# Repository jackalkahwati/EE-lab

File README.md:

# EE-lab

FirstLight: a prompt-to-hardware pipeline (routed, DRC-gated PCBAs plus CAD enclosures, simulation, firmware, and fab packages) and the autonomous bring-up station that tests the boards it produces. This repo holds the planner, the web app, the CLI/MCP client, the marketing site, the station control software, and the hardware/CAD sources.

## Subprojects

| Path | What it is | Run the tests |
|------|------------|---------------|
| `hardware/planner/` | Python planner: spec resolution, part library, netlist synthesis, routing, sim, KiCad export | `pip install -r hardware/planner/requirements.txt && python -m pytest -q hardware/planner` |
| `software/prompt-to-pcb-ui/` | Next.js "Compose" app (the product at app.firstlight.build) and the `/api/v1` API | `cd software/prompt-to-pcb-ui && pnpm install --frozen-lockfile && pnpm typecheck && pnpm lint && pnpm test` |
| `software/firstlight-cli/` | `firstlight` CLI and `firstlight-mcp` MCP server over the v1 API | `cd software/firstlight-cli && npm test` |
| `software/firstlight-website/` | Marketing site (firstlight.build) | `cd software/firstlight-website && npm ci && npm run lint && npm run typecheck` |
| `software/station/` | Bring-up station control software (HAL, engine, API) | `pip install -e "software/station[dev]" && python -m pytest -q software/station` |

`.github/workflows/ci.yml` runs the same commands on every push and pull request.

## Production

Compose runs on a single Mac via launchd behind a Cloudflare tunnel. The runbook, including how to ship new code and which env vars matter, is `software/prompt-to-pcb-ui/deploy/OPS.md`. The `deploy/` READMEs describe future container/VM targets, not what is serving today.

## Review

The audit of the prompt-to-PCB stack and the fixes it drove is in [`docs/prompt-to-pcb-review.md`](docs/prompt-to-pcb-review.md).

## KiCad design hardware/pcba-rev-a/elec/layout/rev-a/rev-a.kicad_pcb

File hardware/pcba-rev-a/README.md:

# FL-1 Relay/Probe Matrix — PCBA Rev A

Electronics project for the FirstLight FL-1 custom board (architecture and
requirements: `relay-probe-matrix-rev-a.md` in this directory).

## Toolchain — same stack as resonant-computer Tile-0

Mirrors `github.com/jackalkahwati/resonant-computer/Tile-0/elec` exactly:

1. **atopile** — schematics as code. `elec/src/*.ato` modules compile to a
   KiCad netlist (`ato build`). Project config: `ato.yaml`.
2. **KiCad 8** — layout in `elec/layout/`, ERC/DRC, custom design rules.
3. **kicad-mcp** — AI-driven placement/routing seeded by
   `elec/layout/.kicad-mcp/project_spec.json` (critical nets, analog
   island, placement intent, 160x100 mm 4-layer outline).
4. **Output pipeline** (as Tile-0 `output/`): gerbers, `bom.csv`,
   `pick_and_place.csv`, `board.step`, ERC/DRC JSON reports, quality-gate
   JSONs, stackup profile.

## Module map

| File | Module | Content |
|---|---|---|
| `main.ato` | `MatrixRevA` | Top level: composition + connectors J2/J20-J24 |
| `power.ato` | `PowerTree` | 24V in -> 5V coil (INA219 shunt) -> 3V3 dig/ana |
| `matrix.ato` | `Matrix`, `LaneSelector` | 8 trees x 11 relays (G6K-2F-Y + reed) |
| `protection.ato` | `ProbeProtection`, `ReferenceBlock` | PTC/TVS/steering, window comparator pre-connect check, cal references |
| `mcu.ato` | `Control` | RP2040 + USB-C + 12x TPIC6B595 + TPS3823 watchdog |
| `cartridge.ato` | `CartridgeInterface` | J10 blind-mate, ID I2C, presence detect |

## Build

```sh
uv tool install atopile          # needs Python >= 3.11
cd hardware/pcba-rev-a
ato build                        # compile -> netlist for KiCad sync
```

## Viewing in KiCad

`elec/layout/rev-a/rev-a.kicad_sch` is the block schematic (valid KiCad 8+
document, plotted clean by kicad-cli) — open with
`open -a KiCad elec/layout/rev-a/rev-a.kicad_sch`. The component-level
schematic materializes when `ato build` syncs the netlist (see gaps).

## MCU decision (2026-06-12)

Rev A uses a **socketed Raspberry Pi Pico 2 module** instead of chip-down
RP2040: kills crystal/QSPI/USB bring-up risk, $5, same silicon. A full
Linux Pi is deliberately not used — relay interlock timing wants an MCU
and the station PC is the smart layer. An Arduino/Pi cannot replace the
board itself: the 88-relay matrix, reed-lane leakage spec, protection
chain, and cartridge contract are the custom content.

## Status / known gaps (Rev A bring-up list)

- BOUND 2026-06-12: 15 real parts created via `ato create part`
  (pty-wrapped, `-s <term> -a`); 172 components on 29 BOM lines, every
  one a real LCSC part. Datasheet-verified pinouts fixed wrong guesses
  on the G6K relay (COM=3 NO=4 NC=2, coil 1/8), reed (coil 5/7, switch
  1/3), TPS54331/7A4901, INA219, BAV99 (node=pin3). Buck/LDO support
  passives added (inductors, boot cap, feedback dividers; COMP/SS
  compensation at analog review). LESSON: never subclass an atomic part
  — footprint paths resolve against the defining file's directory; put
  pin aliases IN the part file (drop is_auto_generated) instead.
  Remaining 9 unbound (documented): 24V entry fuse (needs >=30V PPTC or
  cartridge fuse selection), Pico module + SEAF blind-mate (local parts,
  footprint+symbol files), J2/J20-J24 connectors (assembly-supplied).
  Substitutions to revisit: PAN CHANG SIP-1A05 reeds (unshielded, vs
  Coto/Pickering spec), 0805L010YR PTC (100 mA hold vs 50 mA spec).
- Pin maps on RP2040 QSPI flash and TPS54331 are abbreviated; finalize at
  netlist sync against real symbols (Tile-0 pattern: vendor symbols pulled
  into `output/symbols/`).
- +/-15V clamp rails: source TBD (charge pump vs external) — net stubs in
  `main.ato`, decision before layout.
- J1 USB-C lives in `mcu.ato` (control); J11 MMCX bypass and J25 chassis
  stud are panel-mount, not board-mount — excluded from the netlist.
- 91 coil channels mapped to 96 sink bits; channel map doc goes in
  firmware (`software/station` driver + RP2040 firmware share it).

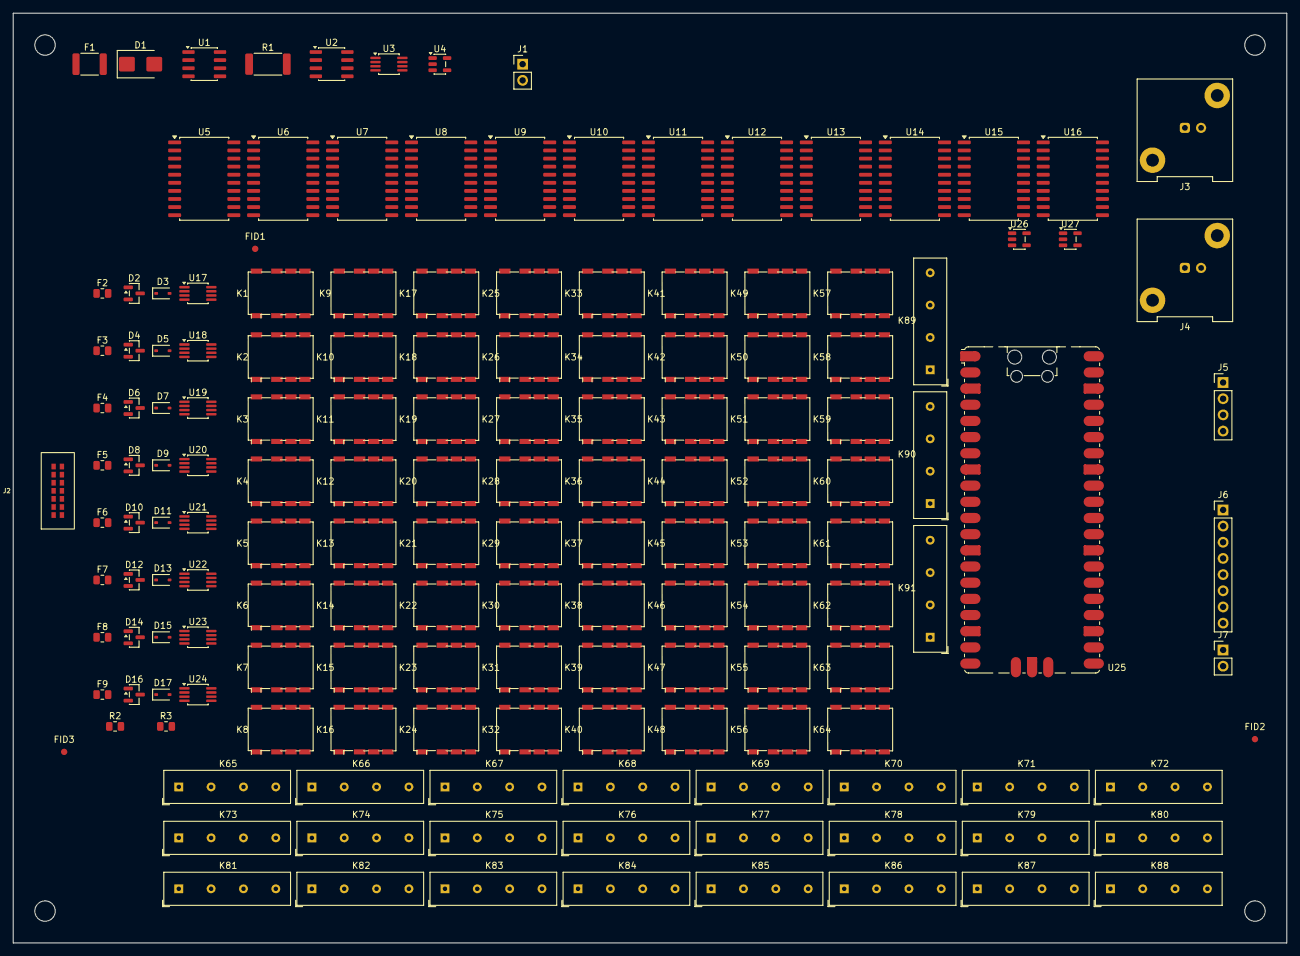
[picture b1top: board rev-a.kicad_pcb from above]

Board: 4 copper layers, 200.0 x 146.0 mm, 157 parts (0 on the bottom side), 46 nets, no tracks yet.

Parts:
D1: D_SMB
D2, D4, D6, D8, D10, D12, D14, D16: SOT-23
D3, D5, D7, D9, D11, D13, D15, D17: D_SOD-323
F1: Fuse_1812_4532Metric
F2, F3, F4, F5, F6, F7, F8, F9: R_0805_2012Metric
FID1, FID2, FID3: Fiducial_1mm_Mask2mm
J1, J7: PinHeader_1x02_P2.54mm_Vertical
J2: SEAF14
J3, J4: BNC_Amphenol_031-5539_Vertical
J5: PinHeader_1x04_P2.54mm_Vertical
J6: PinHeader_1x08_P2.54mm_Vertical
K1, K2, K3, K4, K5, K6, K7, K8, K9, K10, K11, K12, K13, K14, K15, K16, K17, K18, K19, K20, K21, K22, K23, K24, K25, K26, K27, K28, K29, K30, K31, K32, K33, K34, K35, K36, K37, K38, K39, K40, K41, K42, K43, K44, K45, K46, K47, K48, K49, K50, K51, K52, K53, K54, K55, K56, K57, K58, K59, K60, K61, K62, K63, K64: Relay_DPDT_Omron_G6K-2F-Y
K65, K66, K67, K68, K69, K70, K71, K72, K73, K74, K75, K76, K77, K78, K79, K80, K81, K82, K83, K84, K85, K86, K87, K88, K89, K90, K91: Relay_SPST_StandexMeder_SIL_Form1A
R1: R_2512_6332Metric
R2, R3: R_0805_2012Metric
U1, U2: SOIC-8_3.9x4.9mm_P1.27mm
U3, U17, U18, U19, U20, U21, U22, U23, U24: MSOP-8_3x3mm_P0.65mm
U4, U26, U27: SOT-23-5
U5, U6, U7, U8, U9, U10, U11, U12, U13, U14, U15, U16: SOIC-20W_7.5x12.8mm_P1.27mm
U25: RaspberryPi_Pico_SMD_HandSolder

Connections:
+3V3_ANA: D2.3, D4.3, D6.3, D8.3, D10.3, D12.3, D14.3, D16.3, U3.8, U17.8, U18.8, U19.8, U20.8, U21.8, U22.8, U23.8, U24.8
+3V3_DIG: U2.8, U4.5, U25.36, U26.5, U27.5
+5V_COIL: K1.1, K2.1, K3.1, K4.1, K5.1, K6.1, K7.1, K8.1, K9.1, K10.1, K11.1, K12.1, K13.1, K14.1, K15.1, K16.1, K17.1, K18.1, K19.1, K20.1, K21.1, K22.1, K23.1, K24.1, K25.1, K26.1, K27.1, K28.1, K29.1, K30.1, K31.1, K32.1, K33.1, K34.1, K35.1, K36.1, K37.1, K38.1, K39.1, K40.1, K41.1, K42.1, K43.1, K44.1, K45.1, K46.1, K47.1, K48.1, K49.1, K50.1, K51.1, K52.1, K53.1, K54.1, K55.1, K56.1, K57.1, K58.1, K59.1, K60.1, K61.1, K62.1, K63.1, K64.1, K65.1, K66.1, K67.1, K68.1, K69.1, K70.1, K71.1, K72.1, K73.1, K74.1, K75.1, K76.1, K77.1, K78.1, K79.1, K80.1, K81.1, K82.1, K83.1, K84.1, K85.1, K86.1, K87.1, K88.1, K89.1, K90.1, K91.1, R1.1, R1.2, U1.8, U2.1, U3.1, U5.2, U6.2, U7.2, U8.2, U9.2, U10.2, U11.2, U12.2, U13.2, U14.2, U15.2, U16.2
+24V: D1.1, F1.1, F1.2, J1.1, U1.7, U25.39
DAQ_1: J6.1, K4.3, K12.3, K20.3, K28.3, K36.3, K44.3, K52.3, K60.3
DAQ_2: J6.2, K5.3, K13.3, K21.3, K29.3, K37.3, K45.3, K53.3, K61.3
DMM_HI: J5.1, K65.3, K68.3, K71.3, K74.3, K77.3, K80.3, K83.3, K86.3, R2.1, R3.1
DMM_LO: J5.2, K66.3, K69.3, K72.3, K75.3, K78.3, K81.3, K84.3, K87.3
GBANK_KFN: K41.3, K42.4, K43.4, K44.4, K45.4, K46.4, K47.4, K48.4
GBANK_KFP: K33.3, K34.4, K35.4, K36.4, K37.4, K38.4, K39.4, K40.4
GBANK_KSN: K57.3, K58.4, K59.4, K60.4, K61.4, K62.4, K63.4, K64.4
GBANK_KSP: K49.3, K50.4, K51.4, K52.4, K53.4, K54.4, K55.4, K56.4
GBANK_P1: K1.3, K2.4, K3.4, K4.4, K5.4, K6.4, K7.4, K8.4
GBANK_P2: K9.3, K10.4, K11.4, K12.4, K13.4, K14.4, K15.4, K16.4
GBANK_P3: K17.3, K18.4, K19.4, K20.4, K21.4, K22.4, K23.4, K24.4
GBANK_P4: K25.3, K26.4, K27.4, K28.4, K29.4, K30.4, K31.4, K32.4
GND: D1.2, D3.2, D5.2, D7.2, D9.2, D11.2, D13.2, D15.2, D17.2, J1.2, J2.9, J2.10, J2.14, J3.2, J4.2, J5.4, J6.5, J6.6, J6.7, J6.8, J7.2, K89.3, K90.3, K91.3, R2.2, R3.2, U1.4, U2.4, U3.4, U4.2, U5.10, U6.10, U7.10, U8.10, U9.10, U10.10, U11.10, U12.10, U13.10, U14.10, U15.10, U16.10, U17.4, U18.4, U19.4, U20.4, U21.4, U22.4, U23.4, U24.4, U25.38, U26.2, U27.2
GND_REF: J5.3, K67.3, K70.3, K73.3, K76.3, K79.3, K82.3, K85.3, K88.3
LOGIC_1: J6.3, K6.3, K14.3, K22.3, K30.3, K38.3, K46.3, K54.3, K62.3
LOGIC_2: J6.4, K7.3, K15.3, K23.3, K31.3, K39.3, K47.3, K55.3, K63.3
NODE_KFN: D12.1, D13.1, F7.2, K41.4, U22.1
NODE_KFP: D10.1, D11.1, F6.2, K33.4, U21.1
NODE_KSN: D16.1, D17.1, F9.2, K57.4, U24.1
NODE_KSP: D14.1, D15.1, F8.2, K49.4, U23.1
NODE_P1: D2.1, D3.1, F2.2, K1.4, U17.1
NODE_P2: D4.1, D5.1, F3.2, K9.4, U18.1
NODE_P3: D6.1, D7.1, F4.2, K17.4, U19.1
NODE_P4: D8.1, D9.1, F5.2, K25.4, U20.1
OE_N: U5.9, U6.9, U7.9, U8.9, U9.9, U10.9, U11.9, U12.9, U13.9, U14.9, U15.9, U16.9, U25.7, U26.1
PWR_INJ: J7.1, K8.3, K16.3, K24.3, K32.3, K40.3, K48.3, K56.3, K64.3
RCK: U5.12, U6.12, U7.12, U8.12, U9.12, U10.12, U11.12, U12.12, U13.12, U14.12, U15.12, U16.12, U25.6
SCL: J2.12, U4.3, U25.10, U27.1
SCOPE_A: J3.1, K2.3, K10.3, K18.3, K26.3, K34.3, K42.3, K50.3, K58.3
SCOPE_B: J4.1, K3.3, K11.3, K19.3, K27.3, K35.3, K43.3, K51.3, K59.3
SDA: J2.11, U4.1, U25.9, U27.3
SRCK: U5.13, U6.13, U7.13, U8.13, U9.13, U10.13, U11.13, U12.13, U13.13, U14.13, U15.13, U16.13, U25.4
SR_DATA: U5.3, U6.3, U7.3, U8.3, U9.3, U10.3, U11.3, U12.3, U13.3, U14.3, U15.3, U16.3, U25.5
TIP_KFN: F7.1, J2.6
TIP_KFP: F6.1, J2.5
TIP_KSN: F9.1, J2.8
TIP_KSP: F8.1, J2.7
TIP_P1: F2.1, J2.1
TIP_P2: F3.1, J2.2
TIP_P3: F4.1, J2.3
TIP_P4: F5.1, J2.4
WDI: U25.11, U26.4

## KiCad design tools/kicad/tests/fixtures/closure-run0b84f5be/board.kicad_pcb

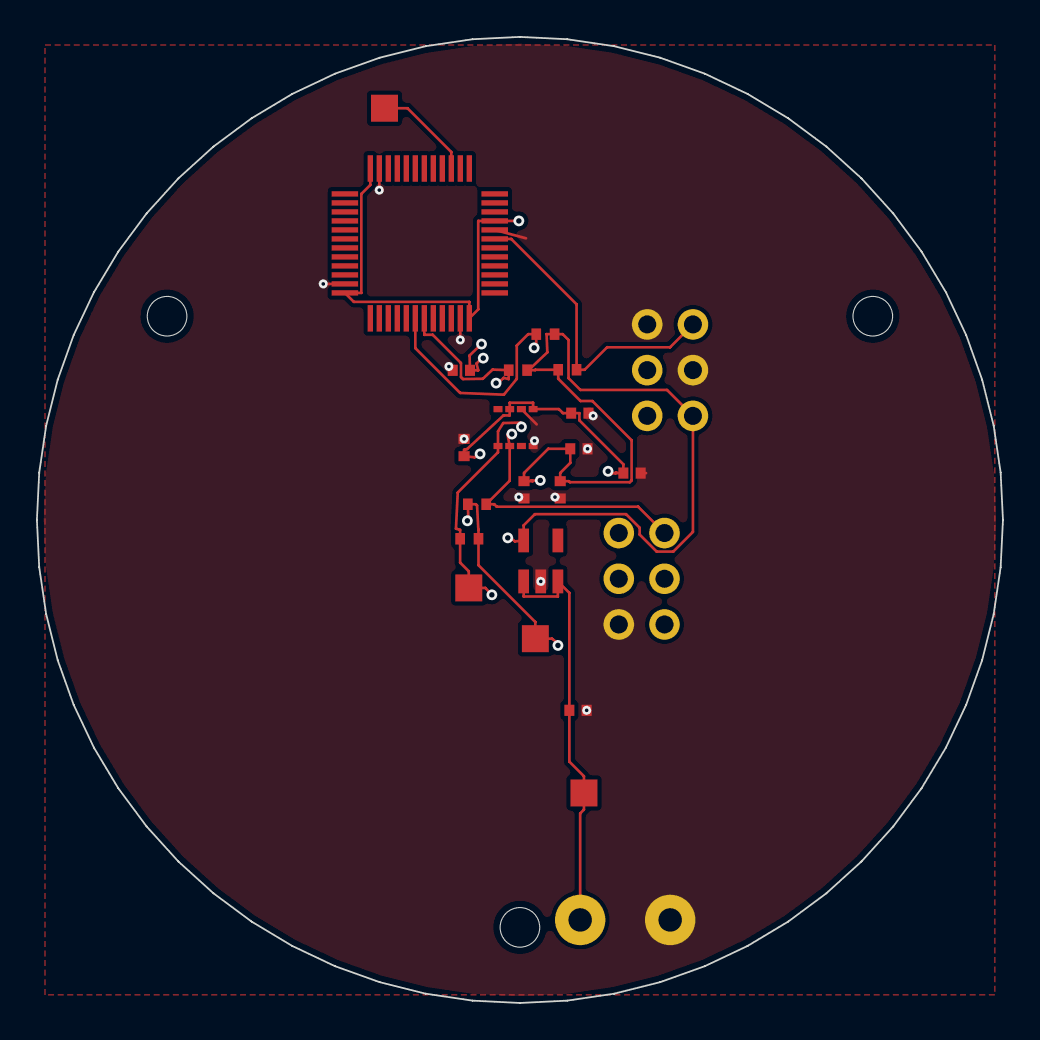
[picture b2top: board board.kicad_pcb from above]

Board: 4 copper layers, 53.7 x 53.7 mm, 23 parts (0 on the bottom side), 9 nets.

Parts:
C2, C3, C4, C5, C9, C10, C12, C13: chip
J1, J20, J21: chip
R10, R11, R12, R90, R91: 10kΩ; resistor
TP1, TP2, TP3, TP4: chip
U1, U2, U3: chip

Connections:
.J1 > .pin2 to .J21 > .pin3: J1.2, J21.3
.J1 > .pin4 to .J21 > .pin4: J1.4, J21.4
.U1 > .pin7 to .R10 > .pin1: J1.5, R10.1, U1.7
.U1 > .pin15 to .TP4 > .pin1: TP4.1, U1.15
.U1 > .pin24 to .U1 > .pin36: C2.1, C3.1, C4.1, C5.1, C10.1, C12.1, C13.1, J1.1, J21.1, R10.2, R11.2, R12.2, R90.2, R91.2, TP2.1, U1.9, U1.24, U1.36, U1.48, U2.5, U3.6, U3.8
.U1 > .pin42 to .R12 > .pin1: J21.6, R12.1, R91.1, TP3.1, U1.42, U3.4
.U1 > .pin43 to .R11 > .pin1: J21.5, R11.1, R90.1, U1.43, U3.3
.U2 > .pin1 to .U2 > .pin3: C9.1, J20.1, TP1.1, U2.1, U2.3
GND: C2.2, C3.2, C4.2, C5.2, C9.2, C10.2, C12.2, C13.2, J1.3, J1.6, J20.2, J21.2, U1.8, U1.23, U1.35, U1.47, U2.2, U3.1, U3.7

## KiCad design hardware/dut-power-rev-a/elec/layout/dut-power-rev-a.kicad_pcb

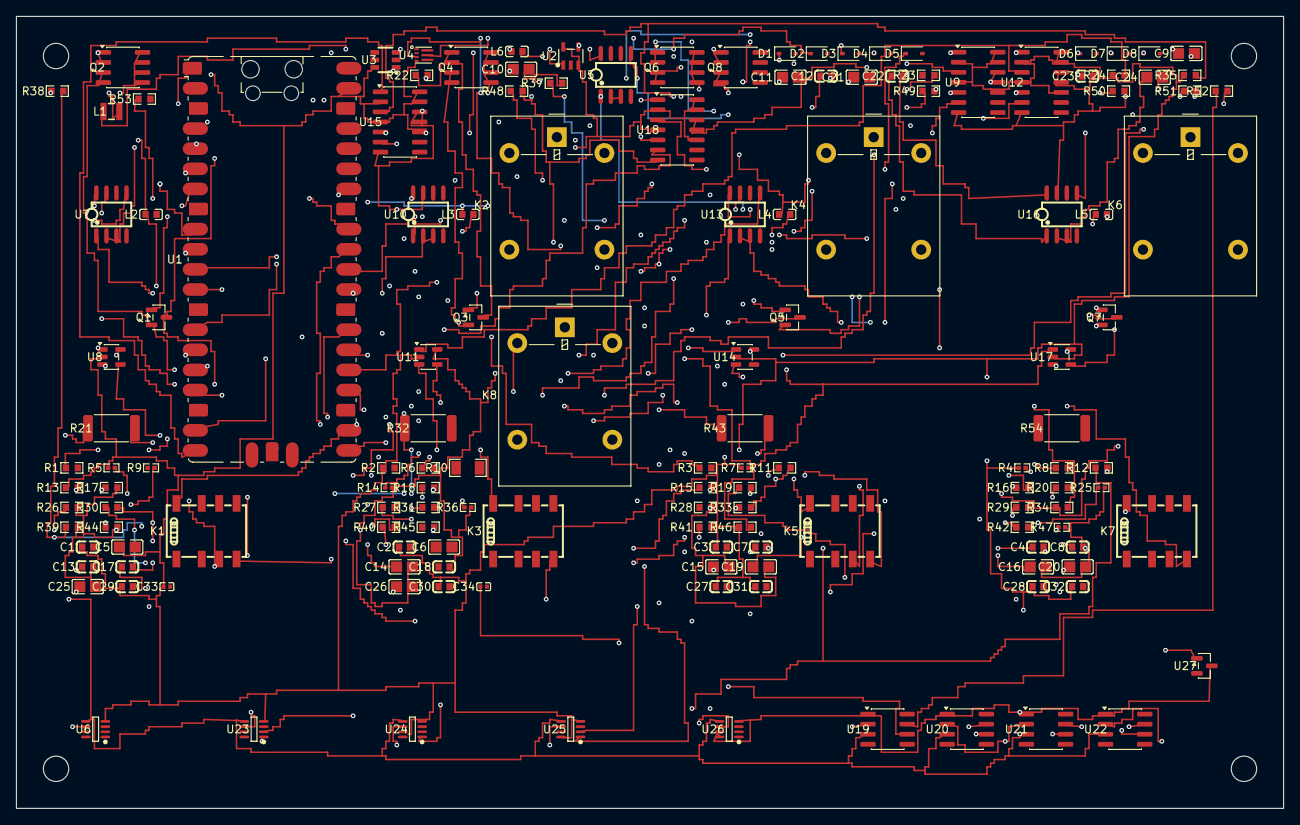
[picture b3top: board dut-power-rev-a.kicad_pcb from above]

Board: 4 copper layers, 160.0 x 100.0 mm, 145 parts (0 on the bottom side), 98 nets.

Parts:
C1, C2, C3, C4, C7, C12, C17, C22, C27, C28, C29, C30, C31, C32: 100nF ±10%; C0603
C5, C6, C9, C10, C11, C14, C15, C16, C19, C20, C21, C24, C25, C26: 47µF ±20%; C0805
C8, C13, C18, C23: 10µF ±10%; C0603
C33, C34: 1µF ±10%; C0402
D1, D2, D3, D4, D5, D6, D7, D8: D_SOD-323_HandSoldering
K1, K3, K5, K7: RELAY-SMD_G6K-2F-X-XX
K2, K4, K6, K8: RELAY-TH_G5LE-1-E
L1: L 2.2µH ±20%; IND-SMD_L2.5-W2.0_MHCHL2520
L2, L3, L4, L5, L6: L 10µH ±20%; L0603
Q1, Q3, Q5, Q7: SOT-23_L2.9-W1.3-P1.90-LS2.4-BR
Q2, Q4, Q6, Q8: SOP-8_L5.0-W4.0-P1.27-LS6.0-BL
R1, R2, R3, R20, R31, R42, R53: 330Ω ±1%; R0603
R4, R5: 4.7kΩ ±1%; R0402
R6: 15.8kΩ ±1%; R0603
R7, R14, R25, R36, R47: 100kΩ ±1%; R0402
R8: 2kΩ ±1%; R0603
R9: 10.5kΩ ±1%; R0402
R10: 50mΩ ±1%; R1206
R11, R12, R13, R19, R22, R23, R24, R30, R33, R34, R35, R41, R44, R45, R46, R52: 10kΩ ±1%; R0603
R15, R26, R37, R48: 100Ω ±1%; R0603
R16, R27, R38, R49: 30kΩ ±1%; R0603
R17, R28, R39, R50: 1kΩ ±1%; R0603
R18, R29, R40, R51: 4.3kΩ ±1%; R0603
R21, R32, R43, R54: R2512
U1: RaspberryPi_Pico_SMD_HandSolder
U2, U8, U11, U14, U17: SOT-23-5_L3.0-W1.7-P0.95-LS2.8-BL
U3: SOT-23-6_L2.9-W1.6-P0.95-LS2.8-BR
U4: VSON-7_L2.0-W2.0-P0.5-TL
U5, U7, U10, U13, U16, U19, U20, U21, U22: SOIC-8_L5.0-W4.0-P1.27-LS6.0-BL
U6, U23, U24, U25, U26: SOT-23-8_L3.0-W1.7-P0.65-LS2.8-BR
U9, U12, U15, U18: SOIC-14_L8.7-W3.9-P1.27-LS6.0-BL
U27: SOT-23-3_L2.9-W1.3-P1.90-LS2.4-BR

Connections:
D: Q1.3, Q2.1, Q2.2, R11.1
EN: U5.2, U5.3
FB: R6.1, R7.2, U4.3
INp: R12.2, R14.1, U8.3
OUT: R13.2, U8.1, U9.3
SCL: R4.2, U1.10, U3.1, U6.5, U19.3, U20.3, U21.3, U22.3, U23.5, U24.5, U25.5, U26.5
SDA: R5.2, U1.9, U3.3, U6.6, U19.2, U20.2, U21.2, U22.2, U23.6, U24.6, U25.6, U26.6
SW: L1.1, U4.6
VSENSE: R8.1, R9.2, U5.5
WDI: U1.11, U2.4
c_boot28-power-hv: C4.1, U5.1
c_boot28-power-lv: C4.2, L2.1, U5.8
c_boot-power-hv: C7.1, U7.1
c_boot-power-hv-1: C12.1, U10.1
c_boot-power-hv-2: C17.1, U13.1
c_boot-power-hv-3: C22.1, U16.1
c_boot-power-lv: C7.2, L3.1, U7.8
c_boot-power-lv-1: C12.2, L4.1, U10.8
c_boot-power-lv-2: C17.2, L5.1, U13.8
c_boot-power-lv-3: C22.2, L6.1, U16.8
c_ilim_filt-power-hv: C8.1, R19.2, U8.4
c_ilim_filt-power-hv-1: C13.1, R30.2, U11.4
c_ilim_filt-power-hv-2: C18.1, R41.2, U14.4
c_ilim_filt-power-hv-3: C23.1, R52.2, U17.4
c_in-power-hv: C9.1, U7.2, U7.3
c_in-power-hv-1: C14.1, U10.2, U10.3
c_in-power-hv-2: C19.1, U13.2, U13.3
c_in-power-hv-3: C24.1, U16.2, U16.3
c_out2-power-hv: C10.1, C11.1, L3.2, Q1.2, Q2.3, Q2.4, R16.1
c_out2-power-hv-1: C15.1, C16.1, L4.2, Q3.2, Q4.3, Q4.4, R27.1
c_out2-power-hv-2: C20.1, C21.1, L5.2, Q5.2, Q6.3, Q6.4, R38.1
c_out2-power-hv-3: C25.1, C26.1, L6.2, Q7.2, Q8.3, Q8.4, R49.1
c_out28-power-hv: C6.1, L2.2, R9.1, R10.1, U4.1, U4.7, U6.1
c_ref_out-power-hv: C34.1, U27.1
cal_uart_tx: R3.1, U1.1
com: K1.3, K2.4, R12.1, R21.2, U23.2
com-1: K3.3, K4.4, R23.1, R32.2, U24.2
com-2: K5.3, K6.4, R34.1, R43.2, U25.2
com-3: K7.3, K8.4, R45.1, R54.2, U26.2
dac_r1_ilim: R19.1, U20.6
dac_r1_vset: R18.1, U22.6
dac_r2_ilim: R30.1, U20.7
dac_r2_vset: R29.1, U22.7
dac_r3_ilim: R41.1, U19.6
dac_r3_vset: R40.1, U21.6
dac_r4_ilim: R52.1, U19.7
dac_r4_vset: R51.1, U21.7
discharge_en: D1.1, K1.8, U1.22
discharge_en-1: D3.1, K3.8, U1.24
discharge_en-2: D5.1, K5.8, U1.25
discharge_en-3: D7.1, K7.8, U1.26
fault_led: R1.1, U1.34
hv: C1.1, C2.1, C3.1, C5.1, C27.1, C28.1, C29.1, C30.1, C31.1, C32.1, C33.1, L1.2, R2.1, R4.1, R5.1, R7.1, R13.1, R24.1, R35.1, R46.1, U1.39, U2.3, U2.5, U3.6, U4.4, U6.4, U8.2, U9.2, U9.4, U9.10, U9.13, U9.14, U11.2, U12.2, U12.4, U12.10, U12.13, U12.14, U14.2, U15.2, U15.4, U15.10, U15.13, U15.14, U17.2, U18.2, U18.4, U18.10, U18.13, U18.14, U19.1, U20.1, U21.1, U22.1, U23.4, U24.4, U24.7, U25.4, U25.8, U26.4, U26.7, U26.8, U27.3
ina_inpos: Q2.5, Q2.6, Q2.7, Q2.8, R21.1, U23.1
ina_inpos-1: Q4.5, Q4.6, Q4.7, Q4.8, R32.1, U24.1
ina_inpos-2: Q6.5, Q6.6, Q6.7, Q6.8, R43.1, U25.1
ina_inpos-3: Q8.5, Q8.6, Q8.7, Q8.8, R54.1, U26.1
led_active: R20.1, U1.27
led_active-1: R31.1, U1.29
led_active-2: R42.1, U1.31
led_active-3: R53.1, U1.32
lv: C1.2, C2.2, C3.2, C5.2, C6.2, C27.2, C28.2, C29.2, C30.2, C31.2, C32.2, C33.2, C34.2, R6.2, R8.2, U1.38, U2.2, U3.2, U3.4, U3.5, U4.5, U5.7, U6.3, U6.7, U6.8, U19.4, U19.8, U20.4, U20.8, U21.4, U21.8, U22.4, U22.8, U23.3, U23.7, U23.8, U24.3, U24.8, U25.3, U25.7, U26.3, U27.2
nRESET: U1.30, U2.1
no: K1.4, R15.1
rail1-VSENSE: R16.2, R17.1, R18.2, U7.5
rail1_enable: D2.1, K2.2, U1.4
rail1_fault_clr: U1.17, U9.1
rail1_fault_n: U1.12, U9.6
rail2-D: Q3.3, Q4.1, Q4.2, R22.1
rail2-INp: R23.2, R25.1, U11.3
rail2-OUT: R24.2, U11.1, U12.3
rail2-VSENSE: R27.2, R28.1, R29.2, U10.5
rail2-no: K3.4, R26.1
rail2-trip_gate: Q3.1, U12.5
rail2_enable: D4.1, K4.2, U1.5
rail2_fault_clr: U1.19, U12.1
rail2_fault_n: U1.14, U12.6
rail3-D: Q5.3, Q6.1, Q6.2, R33.1
rail3-INp: R34.2, R36.1, U14.3
rail3-OUT: R35.2, U14.1, U15.3
rail3-VSENSE: R38.2, R39.1, R40.2, U13.5
rail3-no: K5.4, R37.1
rail3-trip_gate: Q5.1, U15.5
rail3_enable: D6.1, K6.2, U1.6
rail3_fault_clr: U1.20, U15.1
rail3_fault_n: U1.15, U15.6
rail4-D: Q7.3, Q8.1, Q8.2, R44.1
rail4-INp: R45.2, R47.1, U17.3
rail4-OUT: R46.2, U17.1, U18.3
rail4-VSENSE: R49.2, R50.1, R51.2, U16.5
rail4-no: K7.4, R48.1
rail4-trip_gate: Q7.1, U18.5
rail4_enable: D8.1, K8.2, U1.7
rail4_fault_clr: U1.21, U18.1
rail4_fault_n: U1.16, U18.6
trip_gate: Q1.1, U9.5
v5_coil-hv: D1.2, D2.2, D3.2, D4.2, D5.2, D6.2, D7.2, D8.2, K1.1, K2.1, K3.1, K4.1, K5.1, K6.1, K7.1, K8.1, R10.2, U6.2
v_out-lv: C8.2, C9.2, C10.2, C11.2, C13.2, C14.2, C15.2, C16.2, C18.2, C19.2, C20.2, C21.2, C23.2, C24.2, C25.2, C26.2, R11.2, R14.2, R15.2, R17.2, R22.2, R25.2, R26.2, R28.2, R33.2, R36.2, R37.2, R39.2, R44.2, R47.2, R48.2, R50.2, U7.7, U8.5, U9.7, U9.11, U9.12, U10.7, U11.5, U12.7, U12.11, U12.12, U13.7, U14.5, U15.7, U15.11, U15.12, U16.7, U17.5, U18.7, U18.11, U18.12

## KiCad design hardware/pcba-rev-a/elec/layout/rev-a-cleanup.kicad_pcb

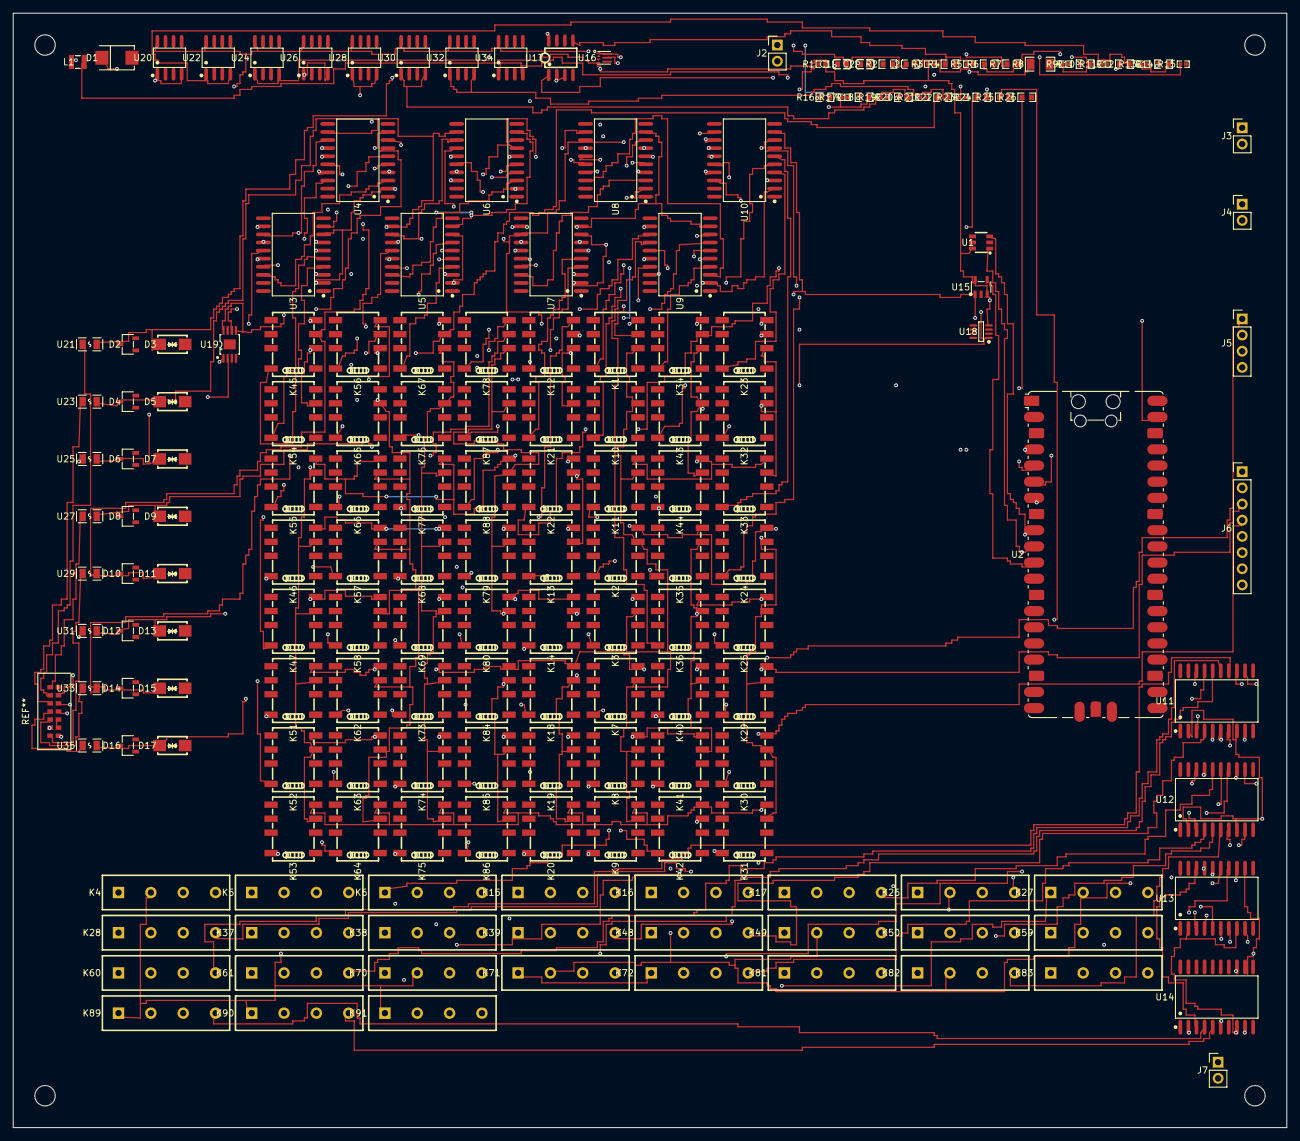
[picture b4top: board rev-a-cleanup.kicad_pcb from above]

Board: 4 copper layers, 200.0 x 175.0 mm, 179 parts (0 on the bottom side), 166 nets.

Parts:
C1: 100nF ±10%; C0603
C2: 10nF ±10%; C0603
D1: SMB_L4.6-W3.6-LS5.3-RD
D2, D4, D6, D8, D10, D12, D14, D16: SOT-23-3_L2.9-W1.6-P1.90-LS2.8-BR
D3, D5, D7, D9, D11, D13, D15, D17: SMA_L4.4-W2.6-LS5.0-BI
J2, J3, J4, J7: PinHeader_1x02_P2.54mm_Vertical
J5: PinHeader_1x04_P2.54mm_Vertical
J6: PinHeader_1x08_P2.54mm_Vertical
K1, K2, K3, K7, K8, K9, K10, K11, K12, K13, K14, K18, K19, K20, K21, K22, K23, K24, K25, K29, K30, K31, K32, K33, K34, K35, K36, K40, K41, K42, K43, K44, K45, K46, K47, K51, K52, K53, K54, K55, K56, K57, K58, K62, K63, K64, K65, K66, K67, K68, K69, K73, K74, K75, K76, K77, K78, K79, K80, K84, K85, K86, K87, K88: RELAY-SMD_G6K-2F-X-XX
K4, K5, K6, K15, K16, K17, K26, K27, K28, K37, K38, K39, K48, K49, K50, K59, K60, K61, K70, K71, K72, K81, K82, K83, K89, K90, K91: RELAY-TH_SIP-1A05
L1: L 2.2µH ±20%; IND-SMD_L2.5-W2.0_MHCHL2520
L2: L 10µH ±20%; L0603
R1: 10kΩ ±1%; R0402
R2: 15.8kΩ ±1%; R0603
R3, R9, R11, R13, R15, R17, R19, R21, R23: 100kΩ ±1%; R0402
R4: 2kΩ ±1%; R0603
R5: 10.5kΩ ±1%; R0402
R6: 20.5kΩ ±1%; R0603
R7: 35.7kΩ ±1%; R0603
R8: 50mΩ ±1%; R1206
R10, R12, R14, R16, R18, R20, R22, R24: 1MΩ ±1%; R0603
R25: 1kΩ ±0.1%; R0603
R26: 100kΩ ±0.1%; R0603
U1: SOT-23-6_L2.9-W1.6-P0.95-LS2.8-BR
U2: RaspberryPi_Pico_SMD_HandSolder
U3, U4, U5, U6, U7, U8, U9, U10, U11, U12, U13, U14: SOIC-20_L13.0-W7.6-P1.27-LS10.3-BL
U15: SOT-23-5_L3.0-W1.7-P0.95-LS2.8-BL
U16: VSON-7_L2.0-W2.0-P0.5-TL
U17: SOIC-8_L5.0-W4.0-P1.27-LS6.0-BL
U18: SOT-23-8_L3.0-W1.7-P0.65-LS2.8-BR
U19: HVSSOP-8_L3.0-W3.0-P0.65-LS4.9-BL-EP_DGN0008D
U20, U22, U24, U26, U28, U30, U32, U34: SOIC-8_L4.9-W3.9-P1.27-LS6.0-BL
U21, U23, U25, U27, U29, U31, U33, U35: F0805

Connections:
C: D1.1, U17.2, U17.3
EN: L2.2, R5.1, R8.1, U16.1, U16.7, U18.1, U19.5, U19.8
FB: R2.1, R3.2, U16.3
IN_Apos: R9.1, R10.2, U20.1, U20.4
RCK: U2.6, U3.12, U4.12, U5.12, U6.12, U7.12, U8.12, U9.12, U10.12, U11.12, U12.12, U13.12, U14.12
SERIN: U2.5, U3.3
SRCK: U2.4, U3.13, U4.13, U5.13, U6.13, U7.13, U8.13, U9.13, U10.13, U11.13, U12.13, U13.13, U14.13
SW: L1.1, U16.6
VSENSE: R4.1, R5.2, U17.5
WDI: U2.11, U15.4
c_boot-power-hv: C1.1, U17.1
c_nr-power-hv: C2.1, U19.6
coil_n: K57.8, U4.7
coil_n-1: K58.8, U4.14
coil_n-2: K62.8, U4.15
coil_n-3: K63.8, U4.16
coil_n-4: K68.8, U5.7
coil_n-5: K69.8, U5.14
coil_n-6: K73.8, U5.15
coil_n-7: K74.8, U5.16
coil_n-8: K79.8, U6.7
coil_n-9: K80.8, U6.14
coil_n-10: K84.8, U6.15
coil_n-11: K85.8, U6.16
coil_n-12: K13.8, U7.7
coil_n-13: K14.8, U7.14
coil_n-14: K18.8, U7.15
coil_n-15: K19.8, U7.16
coil_n-16: K46.8, U3.7
coil_n-17: K2.8, U8.7
coil_n-18: K3.8, U8.14
coil_n-19: K7.8, U8.15
coil_n-20: K8.8, U8.16
coil_n-21: K47.8, U3.14
coil_n-22: K35.8, U9.7
coil_n-23: K36.8, U9.14
coil_n-24: K40.8, U9.15
coil_n-25: K41.8, U9.16
coil_n-26: K51.8, U3.15
coil_n-27: K24.8, U10.7
coil_n-28: K25.8, U10.14
coil_n-29: K29.8, U10.15
coil_n-30: K30.8, U10.16
coil_n-31: K52.8, U3.16
com: K1.2, K2.3, K3.3, K7.3, K8.3, K9.3, K10.3, K11.3
ctl-SERIN: U3.18, U4.3
ctl-SERIN-1: U12.18, U13.3
ctl-SERIN-2: U11.18, U12.3
ctl-SERIN-3: U13.18, U14.3
ctl-SERIN-4: U4.18, U5.3
ctl-SERIN-5: U5.18, U6.3
ctl-SERIN-6: U6.18, U7.3
ctl-SERIN-7: U7.18, U8.3
ctl-SERIN-8: U8.18, U9.3
ctl-SERIN-9: U9.18, U10.3
ctl-SERIN-10: U10.18, U11.3
dmm_hi: J5.1, K4.3, K15.3, K26.3, K37.3, K48.3, K59.3, K70.3, K81.3, K89.1, K90.1, K91.1
dmm_lo: J5.2, K5.3, K16.3, K27.3, K38.3, K49.3, K60.3, K71.3, K82.3
hv: L1.2, R1.2, R3.1, U1.6, U2.39, U3.2, U3.8, U4.2, U4.8, U5.2, U5.8, U6.2, U6.8, U7.2, U7.8, U8.2, U8.8, U9.2, U9.8, U10.2, U10.8, U11.2, U11.8, U12.2, U12.8, U13.2, U13.8, U14.2, U14.8, U15.3, U15.5, U16.4, U18.4
lv: C2.2, D1.2, D3.2, D5.2, D7.2, D9.2, D11.2, D13.2, D15.2, D17.2, J2.2, J7.2, K6.3, K17.3, K28.3, K39.3, K50.3, K61.3, K72.3, K83.3, K91.3, R2.2, R4.2, R6.2, R9.2, R11.2, R13.2, R15.2, R17.2, R19.2, R21.2, R23.2, R25.2, R26.2, U1.2, U1.4, U1.5, U2.38, U3.10, U3.11, U3.19, U4.10, U4.11, U4.19, U5.10, U5.11, U5.19, U6.10, U6.11, U6.19, U7.10, U7.11, U7.19, U8.10, U8.11, U8.19, U9.10, U9.11, U9.19, U10.10, U10.11, U10.19, U11.10, U11.11, U11.19, U12.10, U12.11, U12.19, U13.10, U13.11, U13.19, U14.10, U14.11, U14.19, U15.2, U16.5, U17.7, U18.3, U18.7, U18.8, U19.4, U20.5, U22.5, U24.5, U26.5, U28.5, U30.5, U32.5, U34.5
matrix.sel_kfn-com: K1.4, K4.1, K5.1, K6.1
matrix.sel_kfp-com: K12.2, K13.3, K14.3, K18.3, K19.3, K20.3, K21.3, K22.3
matrix.sel_kfp-com-1: K12.4, K15.1, K16.1, K17.1
matrix.sel_ksn-com: K23.2, K24.3, K25.3, K29.3, K30.3, K31.3, K32.3, K33.3
matrix.sel_ksn-com-1: K23.4, K26.1, K27.1, K28.1
matrix.sel_ksp-com: K34.2, K35.3, K36.3, K40.3, K41.3, K42.3, K43.3, K44.3
matrix.sel_ksp-com-1: K34.4, K37.1, K38.1, K39.1
matrix.sel_p1-com: K45.2, K46.3, K47.3, K51.3, K52.3, K53.3, K54.3, K55.3
matrix.sel_p1-com-1: K45.4, K48.1, K49.1, K50.1
matrix.sel_p2-com: K56.2, K57.3, K58.3, K62.3, K63.3, K64.3, K65.3, K66.3
matrix.sel_p2-com-1: K56.4, K59.1, K60.1, K61.1
matrix.sel_p3-com: K67.2, K68.3, K69.3, K73.3, K74.3, K75.3, K76.3, K77.3
matrix.sel_p3-com-1: K67.4, K70.1, K71.1, K72.1
matrix.sel_p4-com: K78.2, K79.3, K80.3, K84.3, K85.3, K86.3, K87.3, K88.3
matrix.sel_p4-com-1: K78.4, K81.1, K82.1, K83.1
nG: U2.7, U3.9, U4.9, U5.9, U6.9, U7.9, U8.9, U9.9, U10.9, U11.9, U12.9, U13.9, U14.9, U15.1
no: J6.1, K2.4, K13.4, K24.4, K35.4, K46.4, K57.4, K68.4, K79.4
no-1: J6.2, K3.4, K14.4, K25.4, K36.4, K47.4, K58.4, K69.4, K80.4
no-2: J6.3, K7.4, K18.4, K29.4, K40.4, K51.4, K62.4, K73.4, K84.4
no-3: J6.4, K8.4, K19.4, K30.4, K41.4, K52.4, K63.4, K74.4, K85.4
node: D2.3, D3.1, K1.3, R10.1, U21.2
node-1: D4.3, D5.1, K12.3, R12.1, U23.2
node-2: D6.3, D7.1, K23.3, R14.1, U25.2
node-3: D8.3, D9.1, K34.3, R16.1, U27.2
node-4: D10.3, D11.1, K45.3, R18.1, U29.2
node-5: D12.3, D13.1, K56.3, R20.1, U31.2
node-6: D14.3, D15.1, K67.3, R22.1, U33.2
node-7: D16.3, D17.1, K78.3, R24.1, U35.2
power-FB: R6.1, R7.2, U19.2
power-lv: C1.2, L2.1, U17.8
prot_kfp-IN_Apos: R11.1, R12.2, U22.1, U22.4
prot_ksn-IN_Apos: R13.1, R14.2, U24.1, U24.4
prot_ksp-IN_Apos: R15.1, R16.2, U26.1, U26.4
prot_p1-IN_Apos: R17.1, R18.2, U28.1, U28.4
prot_p2-IN_Apos: R19.1, R20.2, U30.1, U30.4
prot_p3-IN_Apos: R21.1, R22.2, U32.1, U32.4
prot_p4-IN_Apos: R23.1, R24.2, U34.1, U34.4
pwr_inj: J7.1, K9.4, K20.4, K31.4, K42.4, K53.4, K64.4, K75.4, K86.4
refs-coil_bus-hv: K89.5, K90.5, K91.5
refs-no: K90.3, R26.1
refs-no-1: K89.3, R25.1
scl: U1.1, U2.10
scope_a: J3.1, K10.4, K21.4, K32.4, K43.4, K54.4, K65.4, K76.4, K87.4
scope_b: J4.1, K11.4, K22.4, K33.4, K44.4, K55.4, K66.4, K77.4, K88.4
sda: U1.3, U2.9
sel_p4-coil_bus-hv: K1.1, K2.1, K3.1, K4.5, K5.5, K6.5, K7.1, K8.1, K9.1, K10.1, K11.1, K12.1, K13.1, K14.1, K15.5, K16.5, K17.5, K18.1, K19.1, K20.1, K21.1, K22.1, K23.1, K24.1, K25.1, K26.5, K27.5, K28.5, K29.1, K30.1, K31.1, K32.1, K33.1, K34.1, K35.1, K36.1, K37.5, K38.5, K39.5, K40.1, K41.1, K42.1, K43.1, K44.1, K45.1, K46.1, K47.1, K48.5, K49.5, K50.5, K51.1, K52.1, K53.1, K54.1, K55.1, K56.1, K57.1, K58.1, K59.5, K60.5, K61.5, K62.1, K63.1, K64.1, K65.1, K66.1, K67.1, K68.1, K69.1, K70.5, K71.5, K72.5, K73.1, K74.1, K75.1, K76.1, K77.1, K78.1, K79.1, K80.1, K81.5, K82.5, K83.5, K84.1, K85.1, K86.1, K87.1, K88.1, R8.2, U18.2
sink_1k: K89.7, U14.4
sink_100k: K90.7, U14.5
sink_kfn_bank: K1.8, U8.4
sink_kfn_dmm_hi: K4.7, U12.17
sink_kfn_dmm_lo: K5.7, U13.4
sink_kfn_gnd: K6.7, U13.5
sink_kfn_pwr: K9.8, U8.17
sink_kfn_scope_a: K10.8, U8.5
sink_kfn_scope_b: K11.8, U8.6
sink_kfp_bank: K12.8, U7.4
sink_kfp_dmm_hi: K15.7, U12.14
sink_kfp_dmm_lo: K16.7, U12.15
sink_kfp_gnd: K17.7, U12.16
sink_kfp_pwr: K20.8, U7.17
sink_kfp_scope_a: K21.8, U7.5
sink_kfp_scope_b: K22.8, U7.6
sink_ksn_bank: K23.8, U10.4
sink_ksn_dmm_hi: K26.7, U13.15
sink_ksn_dmm_lo: K27.7, U13.16
sink_ksn_gnd: K28.7, U13.17
sink_ksn_pwr: K31.8, U10.17
sink_ksn_scope_a: K32.8, U10.5
sink_ksn_scope_b: K33.8, U10.6
sink_ksp_bank: K34.8, U9.4
sink_ksp_dmm_hi: K37.7, U13.6
sink_ksp_dmm_lo: K38.7, U13.7
sink_ksp_gnd: K39.7, U13.14
sink_ksp_pwr: K42.8, U9.17
sink_ksp_scope_a: K43.8, U9.5
sink_ksp_scope_b: K44.8, U9.6
sink_p1_bank: K45.8, U3.4
sink_p1_dmm_hi: K48.7, U11.4
sink_p1_dmm_lo: K49.7, U11.5
sink_p1_gnd: K50.7, U11.6
sink_p1_pwr: K53.8, U3.17
sink_p1_scope_a: K54.8, U3.5
sink_p1_scope_b: K55.8, U3.6
sink_p2_bank: K56.8, U4.4
sink_p2_dmm_hi: K59.7, U11.7
sink_p2_dmm_lo: K60.7, U11.14
sink_p2_gnd: K61.7, U11.15
sink_p2_pwr: K64.8, U4.17
sink_p2_scope_a: K65.8, U4.5
sink_p2_scope_b: K66.8, U4.6
sink_p3_bank: K67.8, U5.4
sink_p3_dmm_hi: K70.7, U11.16
sink_p3_dmm_lo: K71.7, U11.17
sink_p3_gnd: K72.7, U12.4
sink_p3_pwr: K75.8, U5.17
sink_p3_scope_a: K76.8, U5.5
sink_p3_scope_b: K77.8, U5.6
sink_p4_bank: K78.8, U6.4
sink_p4_dmm_hi: K81.7, U12.5
sink_p4_dmm_lo: K82.7, U12.6
sink_p4_gnd: K83.7, U12.7
sink_p4_pwr: K86.8, U6.17
sink_p4_scope_a: K87.8, U6.5
sink_p4_scope_b: K88.8, U6.6
sink_short: K91.7, U14.6
v3v3-hv: R7.1, U19.1, U20.8, U22.8, U24.8, U26.8, U28.8, U30.8, U32.8, U34.8
